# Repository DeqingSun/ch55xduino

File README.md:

*languages: [English](README.md), [简体中文](README.zh-CN.md)*

# Ch55xduino: Small Devices Arduino for ch55x devices

**Getting started on the Ch55x the easy way. Forked from Sduino project, also based on 
ch554_sdcc project**

Ch55xduino is an Arduino-like programming API for the CH55X, a family of low-cost MCS51 USB MCU. The project tries to remove the difficulty of setting up a compiling environment. Users can simply write code in Arduino IDE and hit one button to flash the chip to get code running. No configuration or guesswork needed. 

CH551, CH552, CH554, may be the lowest part count system that works with Arduino. The minimal system only requires one chip, 2 decoupling capacitors, and one optional pull-up resistor. These features made it ideal for DIY projects. 

At this moment the project is still working-in-progress. Support most Arduino functions (Except pulse, shift, tone). Refer to examples in this repo for more info.

## Installation

Automatic IDE integration is supported via the
Arduino Boards Manager. This is the recommanded way of installation now. 

Start the Arduino-IDE. In *File->Preferences*, *Settings* tab, enter

> https://raw.githubusercontent.com/DeqingSun/ch55xduino/ch55xduino/package_ch55xduino_mcs51_index.json

as an *Additional Boards Manager URL*.

* Open *Tools->Board:...->Boards Manager*
* Find Ch55xduino by typing 'ch' into the search line
* Click on the list entry
* Click on *Install*.

Now you should find a new entry *CH55x Boards* in the list at
*Tools->Board:...*

* Choose *CH552 Board* from the list
* open the standard Blink example from *File->Examples->01. Basics->Blink*
* Change pin number in Blink example. For example, if you have LED on P3_0, you will write pin 30.
* compile it by hitting *Verify*
* If your board is never used with ch55xduino before, you need to make the ch55x chip enter bootloader mode. You need to disconnect USB and unpower ch55x, connect the pull-up resistor on D+ line (generally a 10K resistor between D+ and 5V, controlled by a push-button or adjacent pads). Then you connect USB. and hit *Upload*. Also, a blank new chip will enter the bootloader automatically.
* If you have used ch55xduino once and your code doesn't crash the USB subsystem, you can simply press *Upload*. Arduino and the firmware will kick the chip into the bootloader automatically.

### Installation without Github access

If you can not access github directly, use this link to a proxy instead.

> https://gh-proxy.deqing.workers.dev/raw.githubusercontent.com/DeqingSun/ch55xduino/playground/mirror/package_ch55xduino_mcs51_proxy_index.json

### USB and Serial upload

Ch55xduino supports both USB and Serial upload methods. If the USB port of the CH55x chip is connected to a host computer, the USB method is recommended.

It is also possible to upload via serial on UART1 of CH55x chips (except CH551). To set CH55x into bootloader mode automatically, you can connect RTS or DTR of a serial adaptor to an interrupt pin of CH55x with a capacitor, and add bootloader jumping code in the interrupt handler.

If you want to leave the bootloader, you may send the following bytes at 57600 baud. ```57 AB A2 01 00 01 A4```  

### Driver for windows

Since 0.0.10, if your Windows automatically installed the driver from wch.cn for the bootloader (4348,55E0), that is fine. The current upload tool can use the default CH375 driver and co-exist with the official [WCHISPTool](http://www.wch.cn/downloads/WCHISPTool_Setup_exe.html).

If you need to use WinUSB or libusb-win32, the tool will still work.

You can use USB Serial (CDC) driver for the default CDC USB stack (1209,C550). Use [Zadig](https://zadig.akeo.ie/) to install the driver if it did not install automatically.

If you tried to emulate another type of USB device without changing the PID/VID, you may need to uninstall the device before installing a new driver.

### Permission for Linux

By default, Linux will not expose enough permission for Arduino to upload the code with the USB bootloader. Copy ```99-ch55xbl.rules``` in this repo to ```/etc/udev/rules.d/``` and restart your computer. Otherwise, the upload tool may not find the bootloader device.

## Reference board

There is a small CH552 breakout board design in the "pcb" folder. When fabricated with 1.6mm board thickness, some USB receptacle may be too loose for the PCB. Just add some tape behind the USB connector to increase the thickness.

The button footprint was designed for 6mm buttons, but 5mm one works too.

## Difference to regular Arduino

### Pin names:

Regular Arduino uses continuous numbers to code pins on AVR chips. In my opinion, it makes more sense since AVR uses letters as a port name. But MCS51 core uses numbers as port names. So CH55xduino's pins using the following rule. 

```PortNumber*10+PinNumber```

For example, P1.1 is 11, P3.2 is 32.

### Analog input:

CH552 has an 8-bit, 4 channel analog-to-digital converter on pin P1.1, P1.4, P1.5, and P3.2. So the input range is 0~255, not 1023.

By default, all pins on the MCS51 microcontrollers have internal pull-up resistors enabled. You may need to use ```pinMode``` to set the pin to ```INPUT``` to disable the pull-up resistor. 

There is no Analog Pin definition such as A0. Just use 11, 14, 15, or 32 for their analog input feature.

### No polymorph functions:

There is no free C++ compiler for MCS51 chip, we can not use polymorph functions. However, since commit 13402 of SDCC, the generic selection is functional. Ch55xduino supports generic selection since 0.0.11.

If you are using a version higher than 0.0.11, the print function can choose a function according to the parameter's type. 

For example. If you want to print to the USB-CDC virtual serial port, you can do:

```
USBSerial_print(val);	//val: the value to print - any data type
USBSerial_print(val, format)	//specifies the number base (for integral data types) or number of decimal places (for floating point types)
USBSerial_print(charPointer, length)	//specifies the string length to be printed 
```

It is also possible to do ``` USBSerial_println ```. If you want to print to Serial0 or Serial1, just use ``` Serial0_print ``` or ``` Serial1_print ```.

Please note if you pass a character in single quotes, such as ```USBSerial_print(',');```, you will get ```44```. Because that char got promoted to integer type. You need to either use ```USBSerial_print((char)',');``` or ```USBSerial_print(",");```.

They are defined in ```genericPrintSelection.h```.

### Memory model:

Unlike most modern architectures including AVR, MCS51 has 2 RAM regions, internal data memory, and external data memory. For CH552, the internal one is only 256 bytes, and the external one is 1024 bytes.

CH55xduino uses the Large Model for SDCC memory models since version 0.0.17. The Large model will allocate all variables in external RAM by default. Variables stored in internal RAM must be declared with the ```__data``` keyword. 

CH55xduino put the stack in internal RAM. So there isn't much space left for variables. If your variable does need fast access, use ```__data``` when you declare it.  

For the default Arduino setting, 148 bytes are reserved for USB endpoints. There will be 876 bytes usable for external RAM.

You can see the memory mapping by opening the map and mem file generated along with the hex file.

#### Common Pitfalls when Using SDCC

Note that when some function is called from an interrupt service routine it should be preceded by a #pragma NOOVERLAY (if it is not reentrant) . A special note here, int (16 bit) and long (32 bit) integer division, multiplication & modulus operations are implemented using external support routines developed in ANSI-C, if an interrupt service routine needs to do any of these operations then the support routines (as mentioned in a following section) will have to recompiled using the --stack-auto option and the source file will need to be compiled using the --int-long-rent compiler option. [src](http://fivedots.coe.psu.ac.th/~cj/masd/resources/sdcc-doc/SDCCUdoc-11.html)

With SDCC, interrupt service routine function prototypes must be placed in the file that contains main ( ) in order for an vector for the interrupt to be placed in the the interrupt vector space.  It's acceptable to place the function prototype in a header file as long as the header file is included in the file that contains main ( ).  SDCC will not generate any warnings or errors if this is not done, but the vector will not be in place so the ISR will not be executed when the interrupt occurs. [src](https://www.silabs.com/community/mcu/8-bit/knowledge-base.entry.html/2007/11/16/common_pitfalls_when-E7zi)

### Reset Pins

Unlike AVR chips, CH55x will reset when the RST pin is High. The reset pin may be configured as an input pin. But such configuration requires modification of Configuration Information byte, which require an external tool to do so.

## Known issues

.

## Included libraries

Most parts of the Arduino core system and some Arduino libraries are already ported to C-syntax. The resulting API is still very close to the C++ version and porting an existing application is not hard. Refer to the examples that come with the libraries.

#### Communication

* SPI: Real hardware-SPI up to 12MHz.

* SoftI2C: Bit-Bang I2C on any 2 pins.

* WS2812: Bit-Bang WS2812 on any pin. Note some compatible LEDs have different timing and some tweak may be needed. 

#### Sensors

* TouchKey: Internal 6-channel capacitive touch module wrapper with an adaptive baseline algorithm.

## Compatibility with the Arduino world

Since there is no free C++ compiler for the MCS51, it is impossible to do a
full 1:1 port of the whole enviroment as is has been done for the STM32 and
the ESP8266.

This is not a drop-in replacement for an AVR, but thanks to some C
preprocessor magic the programming API is still very, very similar and it is
often enough to just move over the opening bracket of the class
instanciation statement and to replace the dot in a method call for an
underscore. Check the [migration
guide](https://tenbaht.github.io/sduino/api/migration/) for an overview.

## Supported Systems:

Arduino IDE versions 1.8.12 are tested, but
most versions >=1.6.6 should work.

* Windows: Tested on Windows 7 and XP.

* MacOS: Tested on 10.14.

* Linux: Tested on Ubuntu 20.04 LTS.

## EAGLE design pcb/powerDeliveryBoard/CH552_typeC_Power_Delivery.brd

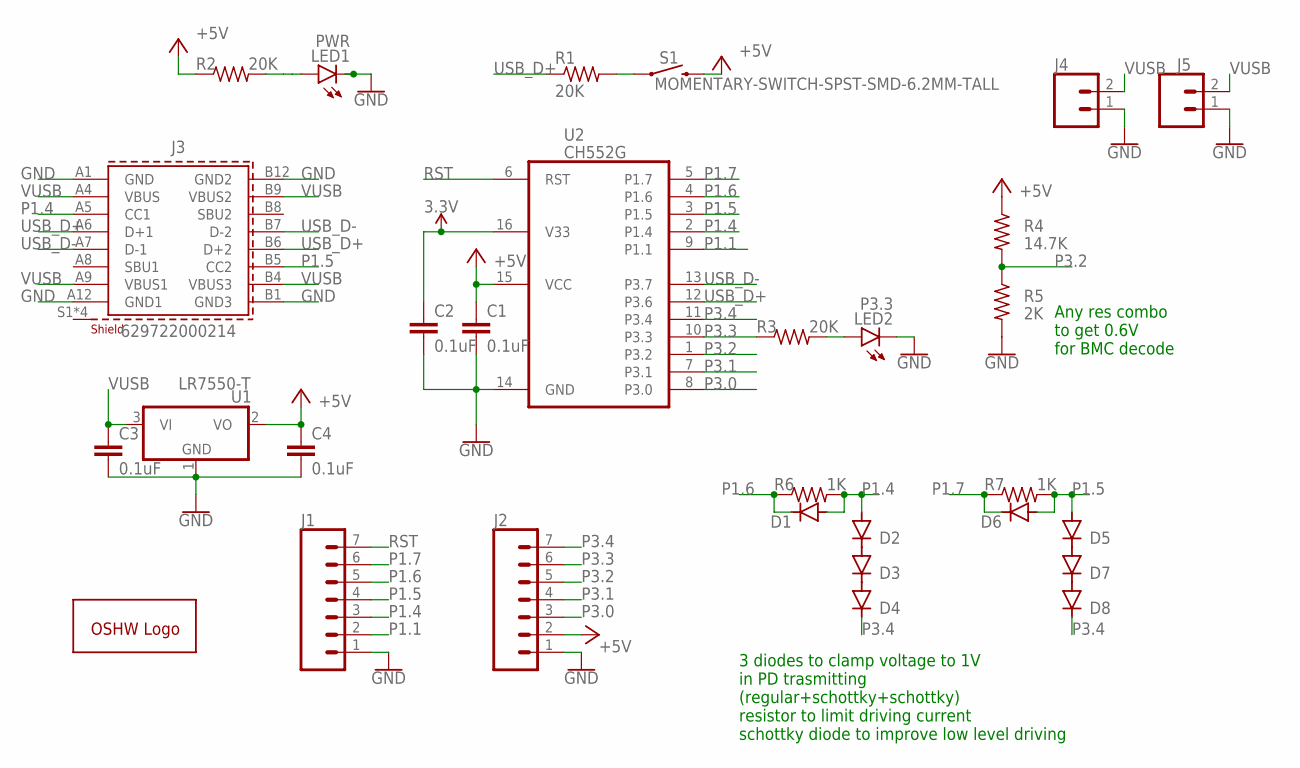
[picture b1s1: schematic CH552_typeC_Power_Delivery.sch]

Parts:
C1, C2, C3, C4: 0.1uF; C0805K; LCSC C16834
D1, D2, D3, D4, D5, D6, D7, D8: DIODE-SOD123; SOD123
GOLD_ORB_SM1: OSHWLOGOLOGO8MM; OSHW_8MM
J1, J2: CONN_07NO_SILK; 1X07_NO_SILK
J3: 629722000214; LCSC C165948 C2765186
J4, J5: CONN_021X02_NO_SILK; 1X02_NO_SILK
LED1: PWR; GHI-BASICCOMPONENTS_0805-LED
LED2: P3.3; GHI-BASICCOMPONENTS_0805-LED
R1, R2, R3: 20K; R0805
R4: 14.7K; R0805
R5: 2K; R0805
R6, R7: 1K; R0805
S1: MOMENTARY-SWITCH-SPST-SMD-6.2MM-TALL; TACTILE_SWITCH_SMD_6.2MM_TALL
U1: MCP1703CB; SOT23
U2: CH552G; MY_IC_SO16; LCSC C111292

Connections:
3.3V: C2.1, U2.16 (V33)
+5V: C1.1, C4.1, J2.2, R2.1, R4.1, S1.B2 (2), U1.2 (VO), U2.15 (VCC)
GND: C1.2, C2.2, C3.2, C4.2, J1.1, J2.1, J3.A1 (GND), J3.A12 (GND1), J3.B1 (GND3), J3.B12 (GND2), J4.1, J5.1, LED1.K, LED2.K, R5.2, U1.1 (GND), U2.14 (GND)
unnamed: R1.2, S1.A2 (1)
unnamed: LED2.A, R3.2
unnamed: LED1.A, R2.2
unnamed: D2.C, D3.A
unnamed: D3.C, D4.A
unnamed: D5.C, D7.A
unnamed: D7.C, D8.A
P1.1: J1.2, U2.9 (P1.1)
P1.4: D1.A, D2.A, J1.3, J3.A5 (CC1), R6.2, U2.2 (P1.4)
P1.5: D5.A, D6.A, J1.4, J3.B5 (CC2), R7.2, U2.3 (P1.5)
P1.6: D1.C, J1.5, R6.1, U2.4 (P1.6)
P1.7: D6.C, J1.6, R7.1, U2.5 (P1.7)
P3.0: J2.3, U2.8 (P3.0)
P3.1: J2.4, U2.7 (P3.1)
P3.2: J2.5, R4.2, R5.1, U2.1 (P3.2)
P3.3: J2.6, R3.1, U2.10 (P3.3)
P3.4: D4.C, D8.C, J2.7, U2.11 (P3.4)
RST: J1.7, U2.6 (RST)
USB_D+: J3.A6 (D+1), J3.B6 (D+2), R1.1, U2.12 (P3.6)
USB_D-: J3.A7 (D-1), J3.B7 (D-2), U2.13 (P3.7)
VUSB: C3.1, J3.A4 (VBUS), J3.A9 (VBUS1), J3.B4 (VBUS3), J3.B9 (VBUS2), J4.2, J5.2, U1.3 (VI)

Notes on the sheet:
Any res combo to get 0.6V for BMC decode
3 diodes to clamp voltage to 1V in PD trasmitting (regular+schottky+schottky) resistor to limit driving current schottky diode to improve low level driving

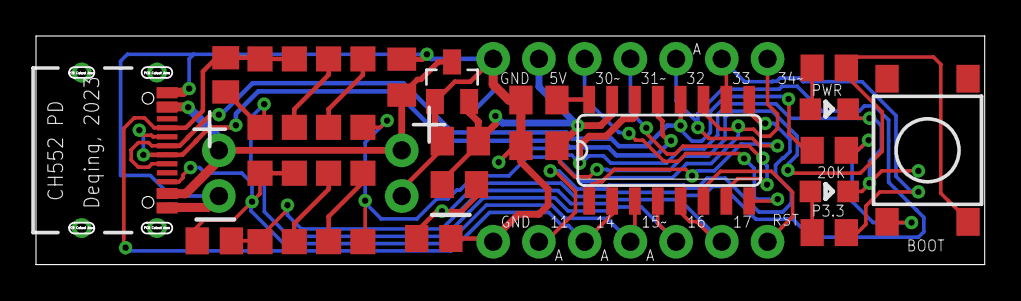
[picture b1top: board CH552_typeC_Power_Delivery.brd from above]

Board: 2 copper layers, 52.6 x 12.6 mm, 30 parts (1 on the bottom side), 24 nets.

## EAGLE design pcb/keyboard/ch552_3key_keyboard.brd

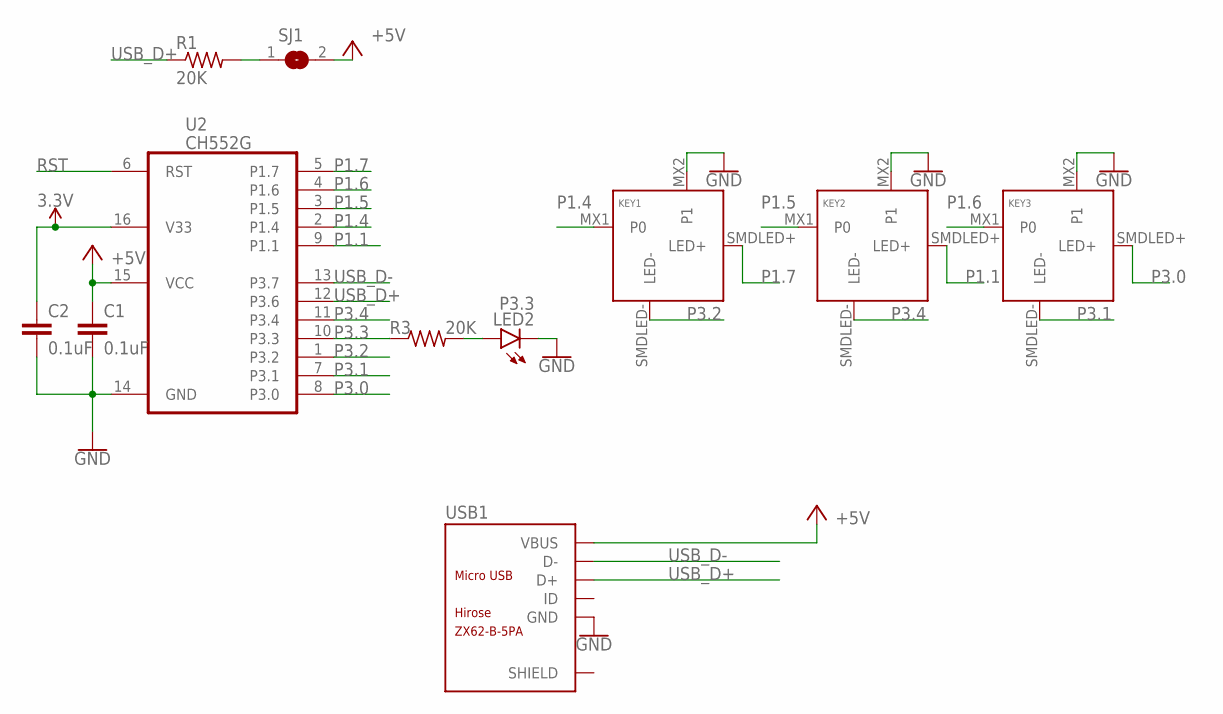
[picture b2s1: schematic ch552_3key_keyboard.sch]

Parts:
C1, C2: 0.1uF; C0805K; LCSC C16834
KEY1, KEY2, KEY3: KEYSWITCH-SMDLED-MXHSPCB-1U-SMDLED; MXHSPCB-1U-SMDLED
LED2: P3.3; GHI-BASICCOMPONENTS_0805-LED
R1, R3: 20K; R0805
SJ1: SJ
U2: CH552G; MY_IC_SO16; LCSC C111292
USB1: ZX62-B-5PA; MICRO-USB5+6P-SMD-0.65-AB; LCSC C10418

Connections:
3.3V: C2.1, U2.16 (V33)
+5V: C1.1, SJ1.2, U2.15 (VCC), USB1.1 (VBUS)
GND: C1.2, C2.2, KEY1.MX2 (P1), KEY2.MX2 (P1), KEY3.MX2 (P1), LED2.K, U2.14 (GND), USB1.5 (GND)
unnamed: R1.2, SJ1.1
unnamed: LED2.A, R3.2
P1.1: KEY2.SMDLED+ (LED+), U2.9 (P1.1)
P1.4: KEY1.MX1 (P0), U2.2 (P1.4)
P1.5: KEY2.MX1 (P0), U2.3 (P1.5)
P1.6: KEY3.MX1 (P0), U2.4 (P1.6)
P1.7: KEY1.SMDLED+ (LED+), U2.5 (P1.7)
P3.0: KEY3.SMDLED+ (LED+), U2.8 (P3.0)
P3.1: KEY3.SMDLED- (LED-), U2.7 (P3.1)
P3.2: KEY1.SMDLED- (LED-), U2.1 (P3.2)
P3.3: R3.1, U2.10 (P3.3)
P3.4: KEY2.SMDLED- (LED-), U2.11 (P3.4)
RST: U2.6 (RST)
USB_D+: R1.1, U2.12 (P3.6), USB1.3 (D+)
USB_D-: U2.13 (P3.7), USB1.2 (D-)

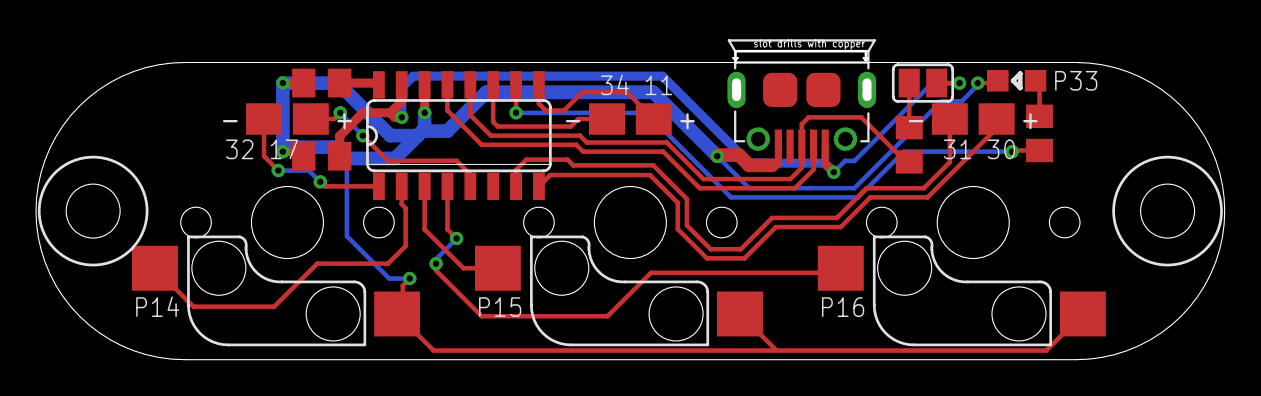
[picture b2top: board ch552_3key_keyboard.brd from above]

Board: 2 copper layers, 65.5 x 17.5 mm, 11 parts (0 on the bottom side), 17 nets.

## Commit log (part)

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2020-12-03 Update README.md
    Created a clean UI to the WebUSB JS Library in ch55xduino/bootloaderWebtool/. I've edited your README.md file to link to the webpage. http://stephenkingston.github.io/CH55x-WebProgrammer/
2021-06-07 Fix Error
2022-03-20 copy proj
2022-03-20 rename
2022-03-20 add id
2022-03-20 add media control
2022-03-25 update delayMicroseconds for 16M and 24M
2022-03-25 add 56M
2022-03-31 add verbose to echo
2022-04-01 Add Serial 1 support
2022-04-01 add bUD_DP_PD_DIS for CH559 in examples
2022-04-01 add name
2022-04-01 avoid unreferenced function argument warning
2022-04-01 add 2 interrupt handlers, need more test
2022-04-04 ch559 start to work
2022-04-04 add tbd for ch559 eeprom
2022-04-04 prevent Serial1_write race hazard
    if uart1IntTxHandler run between Serial1_write on 2nd char, the queue will corrupt
2022-04-04 prevent Serial0_write race hazard
    serial0 not likely, as TI trigger after serial byte write, while U1TI trigger when byte write starts
2022-04-04 add CH549 UART1
2022-04-06 fix 2.5.0 bug, maybe more bugs in bootloader
2022-04-06 fine tune delayMicroseconds and fix bugs
2022-04-06 add keyboard mouse example
2022-04-23 sync playground and main
2022-04-23 add generic function
2022-04-23 update examples
2022-04-23 select different args
2022-04-23 add generic for 2 args
2022-04-23 add serial 0 and 1 support
2022-05-01 simplify sdcc.sh by not copy cpp
    https://github.com/tenbaht/sduino/issues/120
2022-05-03 include dummy_variable_main
2022-05-06 edit rel file
2022-05-06 update GSFINAL
2022-05-06 fix sed, check CSEG
2022-05-06 edit for busybox (ash)
2022-05-18 update tool
2022-05-18 update for external osc, need testing
2022-05-23 fix turnOffPWM bug
2022-09-17 add spi flash
2022-09-17 add 12M support
2022-09-17 check sed version on mac
2022-09-17 add retry in upload
    https://github.com/DeqingSun/ch55xduino/issues/76
2022-10-19 fix GSINIT in sdcc.sh
    volatile variable may create odd length code in GSINIT
2022-10-19 add 266 bytes USB ram option.
2022-11-03 use even to fit fixed linker
2022-11-05 Add USBtinySPI_CH552 example
2023-01-30 sync with main
2023-02-05 edit files for sdcc update but encounter bug
2023-02-12 Allow inclusion of Hardware Serial by menu item
2023-02-16 Move 'No UART' to the end so UART0 is the default.
2023-02-17 Reverse UARTx to NO_UARTx logic
2023-04-17 import main update
2023-04-17 change model to large
2023-04-18 change back to small for now
2023-04-18 change to large and int-long-reent
    use float sdcc and mcs51 lib as is but use int long longlong from stackauto
2023-04-18 clean wiring_digital to eliminate extra code size
2023-04-18 add __data for some files
2023-04-19 fix all print
2023-04-19 fix all core lib
2023-04-24 add addlib script
2023-04-24 update tool binary
2023-04-24 update gen script
2023-05-10 update from main
2023-05-10 Add 0 packet to end bulk when previous packet was 64
2023-05-19 duplicate keyboard example
2023-05-19 fix keyboard mouse combo warning
2023-05-19 update combo more
2023-05-19 update media keyboard
2023-05-19 update datatype for qmk
2023-05-19 move user lib
2023-05-19 update description for raw HID
2023-05-19 add a test json
2023-05-19 copy os detect code
2023-05-19 add some print data for test
2023-05-19 via start to work
2023-05-19 flash OK
2023-05-19 extract dynamic_keymap_get_keycode for reuse
2023-05-20 add typeA connector pcb
2023-05-23 move config to h file
2023-05-23 add PID VID to config
2023-05-24 via seems refuse to use shared interface
2023-05-24 update but not work yet
2023-05-25 not crash computer
2023-05-25 enable endpoint2
2023-05-25 bump version to 1 to make via happy
2023-05-26 add 3 key keyboard
2023-05-26 Add text
2023-05-26 almost work, keypress map incorrect
2023-05-26 keyboard working
2023-05-26 update comments
2023-05-28 use struct for DevDesc
2023-05-28 remove string length
2023-05-28 move file
2023-05-29 convert ConfigurationDescriptor to LUFA style
2023-05-29 update Descriptor
2023-06-02 add target to avoid write to wrong chip
2023-06-02 remove CfgDescLen
2023-06-02 update CDCinUserCode in Lufa style
2023-06-02 change keyboard to lufa style
2023-06-02 do not send unknown string
2023-06-02 add UsbConfig
2023-06-02 convert keyboard mouse to lufa style
2023-06-02 update media keyboard to lufa
2023-06-02 change mass storage to lufa style
2023-06-02 convert to LUFA descriptor
2023-06-04 fix slow config
    Serial print without begin will be extremely slow.
2023-06-20 Add 6Mhz clock support
2023-06-21 update pins
2023-06-21 format code
2023-06-21 add protect
2023-06-23 add support for 32M clk
2023-06-23 get started for PD, ready to parse data from charger
2023-06-24 clean code
2023-06-24 capture 2 cc pins
2023-06-25 CH549 can print data from CC
2023-06-25 check SOP
2023-06-26 move functions to pd.c
2023-06-26 format code with struct
2023-06-26 need to calculate crc
2023-06-27 convert all received data to original
2023-06-27 data not correct
2023-06-28 crc32 work for 1 byte
2023-06-28 fix crc jmp error
2023-06-28 can respond but no further step
2023-06-29 decode in separate function
2023-06-29 can parse data
2023-06-29 try to send back, no respond yet
2023-06-29 add 32M delay
2023-06-29 Add EOP
2023-06-30 update comment
2023-06-30 update recv routine
2023-06-30 Try 16M, not working yet
2023-06-30 doesn't work for 24M
2023-06-30 dup 552 circuit as start of ch549
2023-06-30 update pins in text editor
2023-06-30 change text
2023-06-30 adjust pins
2023-06-30 update board
2023-07-01 try to assembly optimize. sync seems working
2023-07-01 can sync output bits
2023-07-01 now sync with bit
2023-07-01 get end of preamble
2023-07-01 change debug to 8M
2023-07-01 not work yet
2023-07-01 almost there
2023-07-01 fix more
2023-07-01 recv work
2023-07-02 work for 24M!
2023-07-02 board finish
2023-07-05 start to try CH552
2023-07-05 CH552 can parse message
2023-07-05 convert send to assembly
2023-07-05 add SndDone
2023-07-06 work for 32M but still not 24M on small charger
2023-07-06 add error comment
2023-07-06 add timing comment
2023-07-07 optimize RcvBufDecode5B4B
2023-07-07 create function
2023-07-07 optimize code
2023-07-07 remove test code
2023-07-07 add comment
2023-07-08 change filename
2023-07-08 copy 552 as beginning
2023-07-09 make some progress
2023-07-12 fix ws2812 include order
2023-07-18 add photo and 3d model
2023-07-23 can parse pps
2023-07-23 change match logic
2023-07-23 PPS almost work
2023-07-23 fixed seems a compiler error
2023-07-23 update code
2023-07-23 remove debug code
2023-07-23 not sure why not pull down?
2023-07-25 move files
2023-07-25 protect include
2023-07-25 protect more
2023-07-25 translate code
2023-07-25 add img
2023-07-26 add imges
2023-08-19 添加中文readme
2023-09-27 update to main
2023-09-27 Add servo library (brief)
2023-09-28 add pulse in
2023-10-04 update servo lib
2023-11-12 made some progress
2023-11-12 some more progress
    set report ready but we need to make in on EP0 work
2023-11-14 remove out endpoint
2023-11-15 improve EP_OUT_0
2023-11-16 init combo from CDC
2023-11-19 edit keyboard interface
2023-11-20 Keyboard work
2024-03-25 add ch554 sound card from ziv2013
    https://github.com/DeqingSun/ch55xduino/issues/155
2024-03-28 update string
2024-03-28 change to mono
2024-03-28 clean up code
2024-03-28 update sample rate
2024-03-29 speaker start to work
2024-03-29 remove noise due to PWM bug
2024-03-29 remove noise on beginning due to Out Of Bounds
2024-03-29 add clang-format
2024-03-29 clang-format
2024-03-29 pull misc update
2024-03-29 pull tiny isp fix
2024-03-29 pull format
2024-04-01 pull update
2024-04-02 add zero cross interval
2024-04-04 add freq detection
2024-05-17 Add CH558 support; cursory tested on CH558L -- only 'substantive' change sofar is teh 64 to 48k memory of flash and the 4k XRAM sizes.
2024-05-17 Add open drain.
2024-05-17 Forgot to include the variant files
2024-05-17 Fix PU flags
2024-05-17 Correct sizes shown
2024-05-18 Further tweaks to differ between CH558/559
2024-07-26 qingcloud not usable
2024-07-26 update json and cloudflare script
2024-08-09 change i2c to wrapper
2024-08-09 add seg 7
2024-08-09 add tool
2024-10-07 fix dwCaptureWidths for 16M
2024-10-08 remove one layer of call
2024-10-08 inline to reduce stack preservation for t2 intr
2024-10-08 extra time for recapture after recv byte
2024-10-09 further optimize
2024-10-10 change compensation
2025-06-08 dup absolute mouse from regular keyboard
2025-06-08 add absolute mouse move from serial
2025-06-09 add LED and button release
2025-06-13 add pn532 to read ID
2025-06-14 add mifare classic ultralight read/write
2025-06-26 reset XY after movement
2025-06-28 support consumer keys
2026-01-26 add remote wakeup for HIDKeyboard
    no key report in wakeup
2026-02-02 fix race hazard in UpPoint2BusyFlag
    If the interrupt happen before the UpPoint2BusyFlag = 1, the UpPoint2BusyFlag will stay 1 forever.
2026-02-02 protect endpoint flag from interrupt
2026-02-02 set flag before ACK

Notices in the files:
parts and their libraries:
SparkFun-PowerSymbols: Licensing: Creative Commons ShareAlike 4.0 International - https://creativecommons.org/licenses/by-sa/4.0
Wurth_Connectors_WR-USB: Copyright: Würth Elektronik
